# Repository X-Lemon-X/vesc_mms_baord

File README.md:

## Board  addaptr for VESC V6.2 to Modu Card system

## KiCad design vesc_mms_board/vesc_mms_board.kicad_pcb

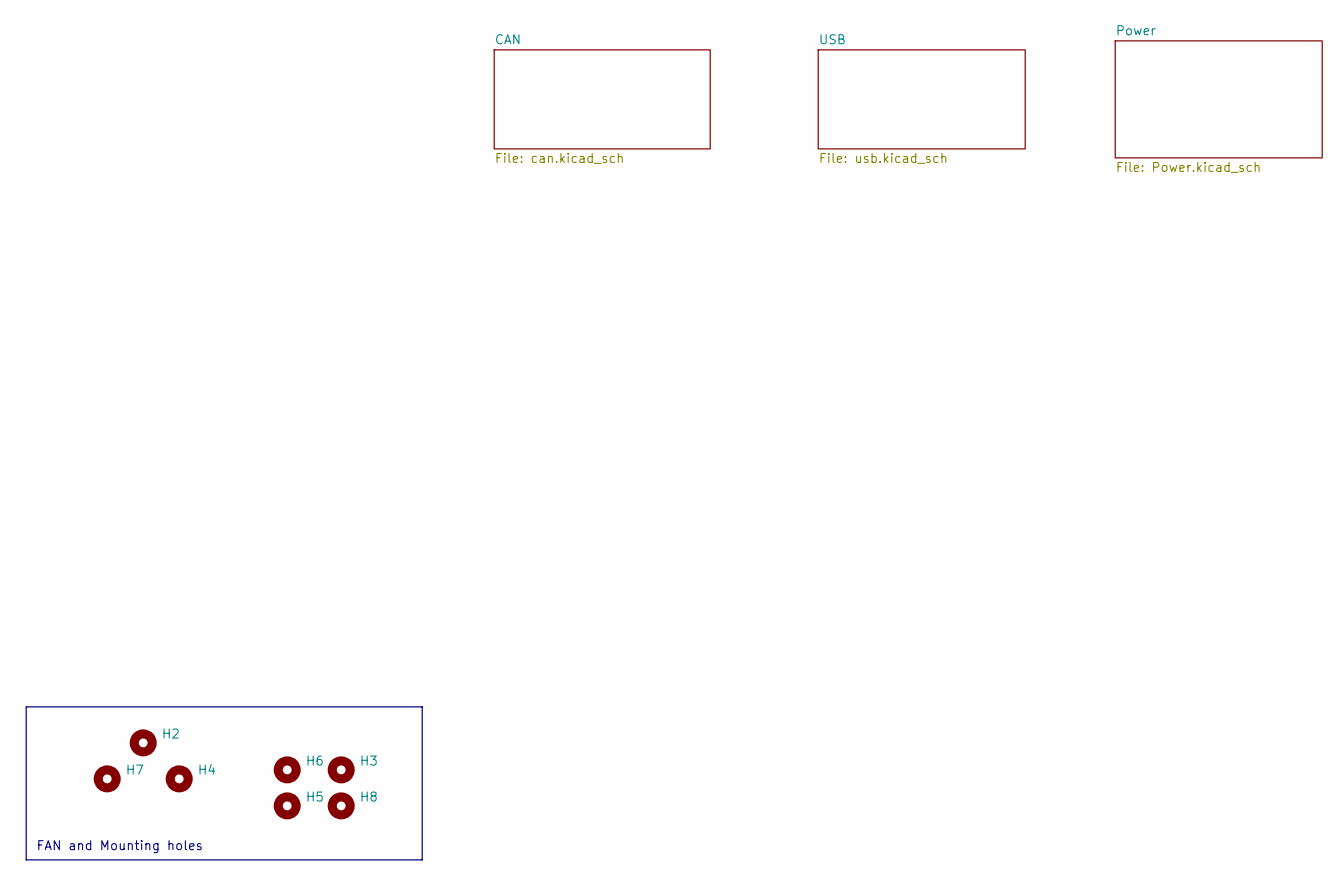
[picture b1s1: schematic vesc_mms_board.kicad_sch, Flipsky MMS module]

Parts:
H2, H4, H7: MountingHole; MountingHole_4.3mm_M4
H3, H5, H6, H8: MountingHole; MountingHole_3.5mm

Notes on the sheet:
FAN and Mounting holes

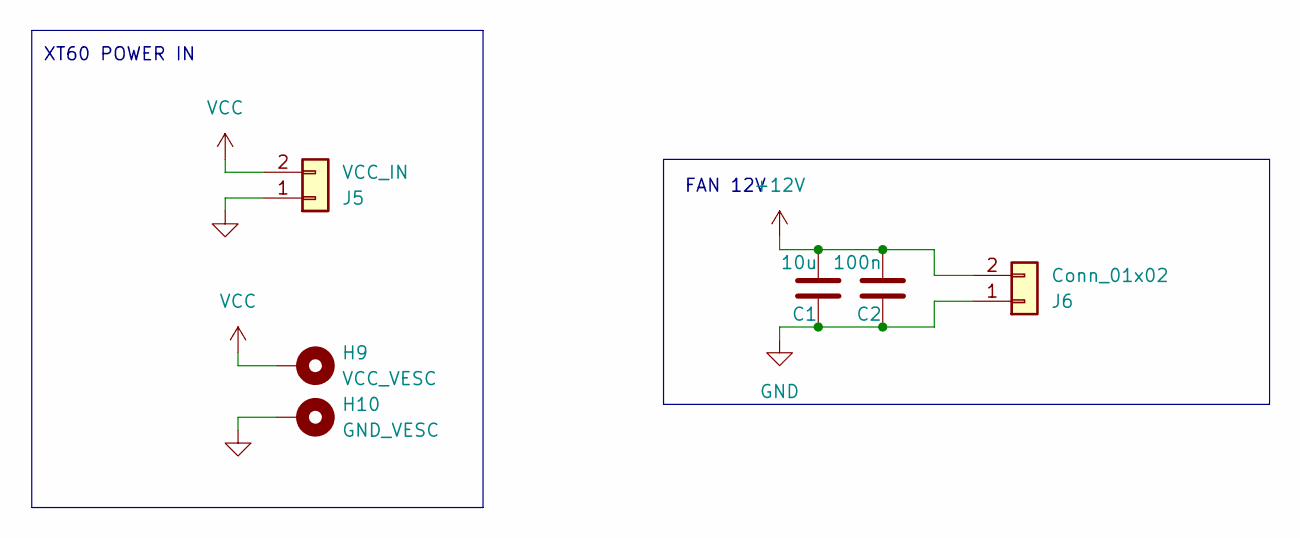
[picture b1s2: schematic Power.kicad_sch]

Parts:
C1: 10u; C_0603_1608Metric
C2: 100n; C_0402_1005Metric
H9: VCC_VESC; MountingHole_4mm_Pad_Via
H10: GND_VESC; MountingHole_4mm_Pad_Via
J5: VCC_IN; AMASS_XT60PW-M_1x02_P7.20mm_Horizontal
J6: Conn_01x02; JST_XH_B2B-XH-A_1x02_P2.50mm_Vertical

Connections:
+12V: C1.2, C2.2, J6.2; also elsewhere on the board
GND: C1.1, C2.1, H10.1, J5.1, J6.1; also elsewhere on the board
VCC: H9.1, J5.2

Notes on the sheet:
FAN 12V
XT60 POWER IN

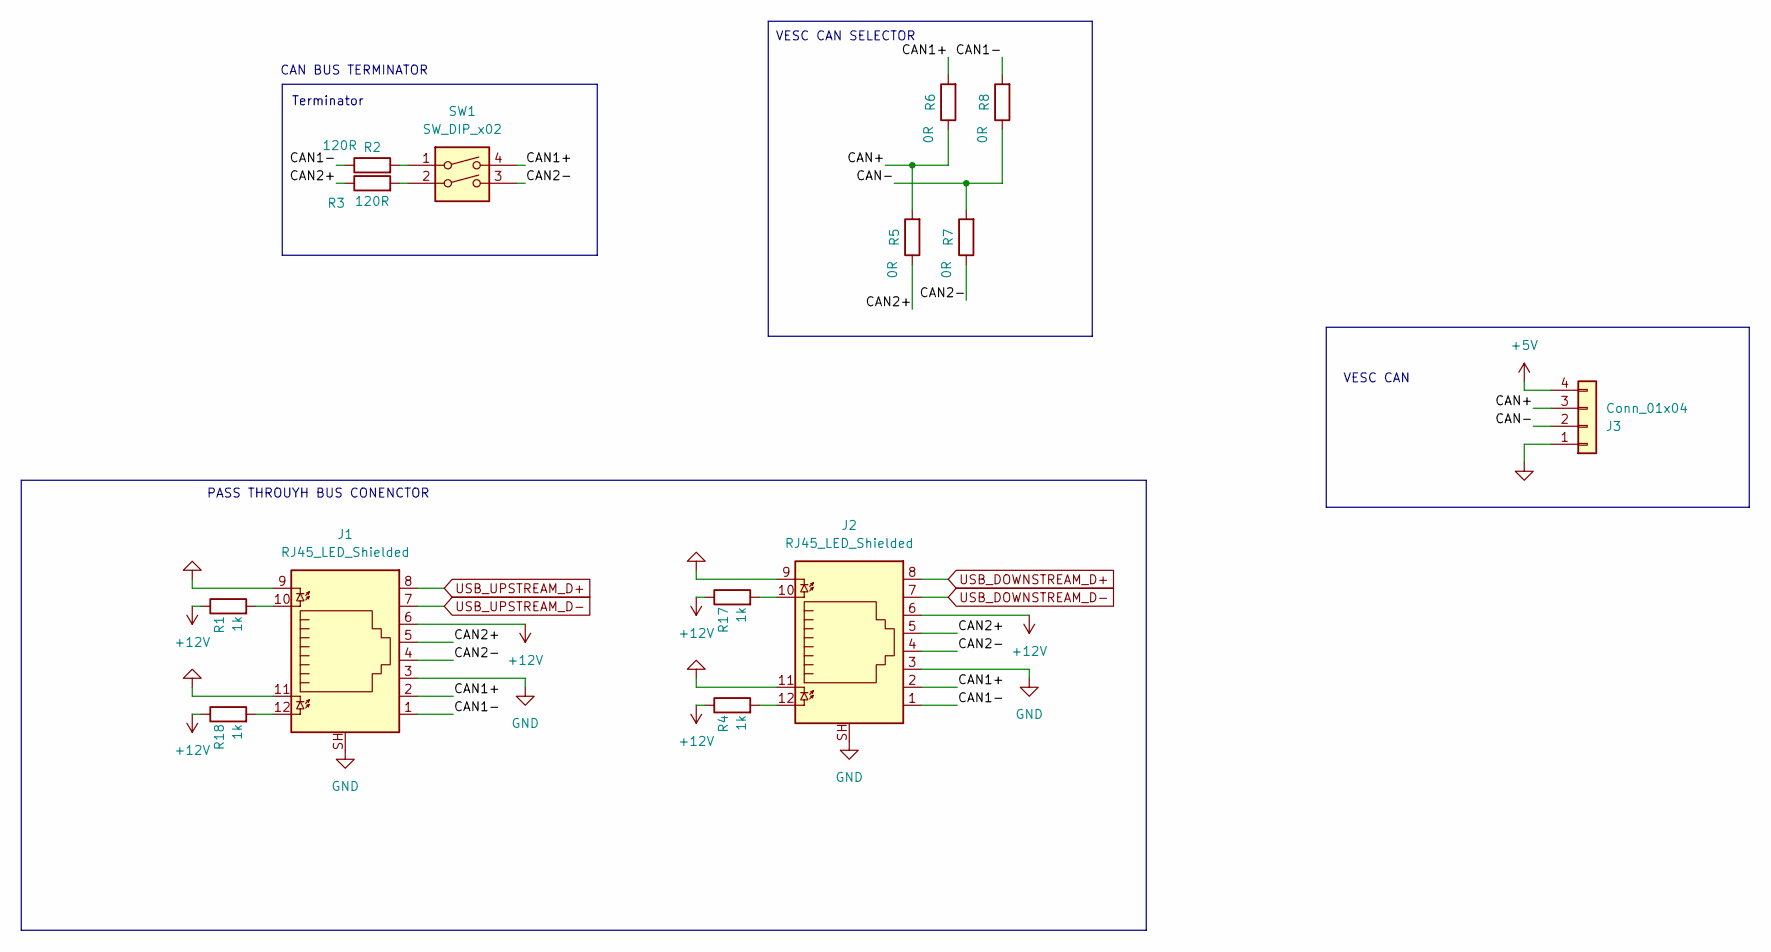
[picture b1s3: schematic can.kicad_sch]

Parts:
J1, J2: RJ45_LED_Shielded; RJ45_Amphenol_RJHSE538X
J3: Conn_01x04; JST_XH_B4B-XH-A_1x04_P2.50mm_Vertical
R1, R4, R17, R18: 1k; R_0402_1005Metric
R2, R3: 120R; R_0603_1608Metric
R5, R6, R7, R8: 0R; R_0603_1608Metric
SW1: SW_DIP_x02; SW_DIP_SPSTx02_Slide_6.7x6.64mm_W7.62mm_P2.54mm_LowProfile

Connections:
+5V: J3.4; also elsewhere on the board
+12V: J1.6, J2.6, R1.1, R4.1, R17.1, R18.1; also elsewhere on the board
/CAN/CAN1+: J1.2, J2.2, R6.2, SW1.4
/CAN/CAN1-: J1.1, J2.1, R2.1, R8.2
/CAN/CAN2+: J1.5, J2.5, R3.1, R5.1
/CAN/CAN2-: J1.4, J2.4, R7.1, SW1.3
/CAN/CAN+: J3.3, R5.2, R6.1
/CAN/CAN-: J3.2, R7.2, R8.1
GND: J1.3, J1.9, J1.11, J1.SH, J2.3, J2.9, J2.11, J2.SH, J3.1; also elsewhere on the board
unnamed: J1.10, R1.2
unnamed: J1.12, R18.2
unnamed: J2.10, R17.2
unnamed: J2.12, R4.2
unnamed: R2.2, SW1.1
unnamed: R3.2, SW1.2
USB_DOWNSTREAM_D+: J2.8; also elsewhere on the board
USB_DOWNSTREAM_D-: J2.7; also elsewhere on the board
USB_UPSTREAM_D+: J1.8; also elsewhere on the board
USB_UPSTREAM_D-: J1.7; also elsewhere on the board

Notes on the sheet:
PASS THROUYH BUS CONENCTOR
CAN BUS TERMINATOR
VESC CAN
Terminator
VESC CAN SELECTOR

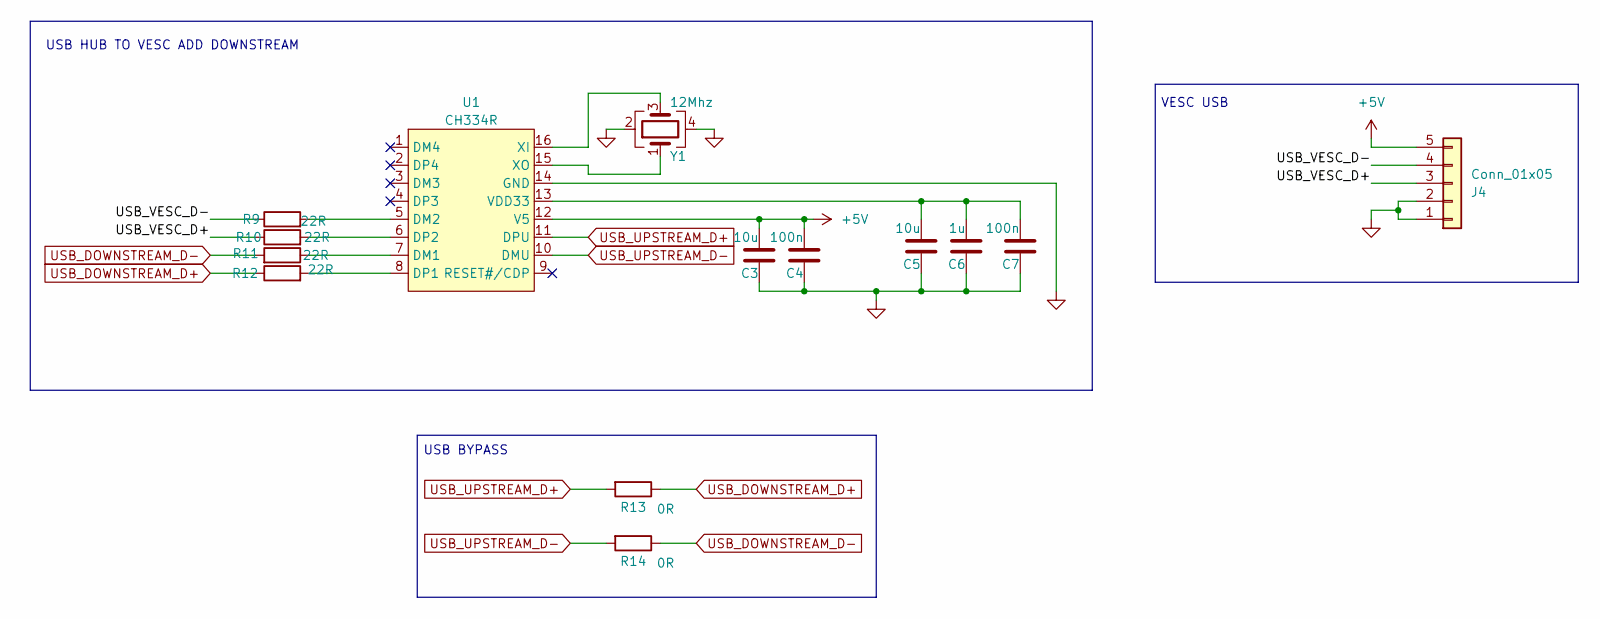
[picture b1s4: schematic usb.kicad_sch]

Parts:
C3, C5: 10u; C_0603_1608Metric
C4, C7: 100n; C_0402_1005Metric
C6: 1u; C_0603_1608Metric
J4: Conn_01x05; JST_XH_B5B-XH-A_1x05_P2.50mm_Vertical
R9, R10, R11, R12: 22R; R_0402_1005Metric
R13, R14: 0R; R_0603_1608Metric
U1: CH334R; QSOP-16_3.9x4.9mm_P0.635mm
Y1: 12Mhz; Crystal_SMD_3225-4Pin_3.2x2.5mm

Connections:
+5V: C3.2, C4.2, J4.5, U1.12 (V5); also elsewhere on the board
/USB/USB_VESC_D+: J4.3, R10.1
/USB/USB_VESC_D-: J4.4, R9.1
GND: C3.1, C4.1, C5.1, C6.1, C7.1, J4.1, J4.2, U1.14 (GND), Y1.2, Y1.4; also elsewhere on the board
unnamed: R11.1, U1.7 (DM1)
unnamed: R9.2, U1.5 (DM2)
unnamed: R12.2, U1.8 (DP1)
unnamed: R10.2, U1.6 (DP2)
unnamed: C5.2, C6.2, C7.2, U1.13 (VDD33)
unnamed: U1.16 (XI), Y1.3
unnamed: U1.15 (XO), Y1.1
USB_DOWNSTREAM_D+: R12.1, R13.1; also elsewhere on the board
USB_DOWNSTREAM_D-: R11.2, R14.1; also elsewhere on the board
USB_UPSTREAM_D+: R13.2, U1.11 (DPU); also elsewhere on the board
USB_UPSTREAM_D-: R14.2, U1.10 (DMU); also elsewhere on the board

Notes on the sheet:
USB BYPASS
USB HUB TO VESC ADD DOWNSTREAM
VESC USB

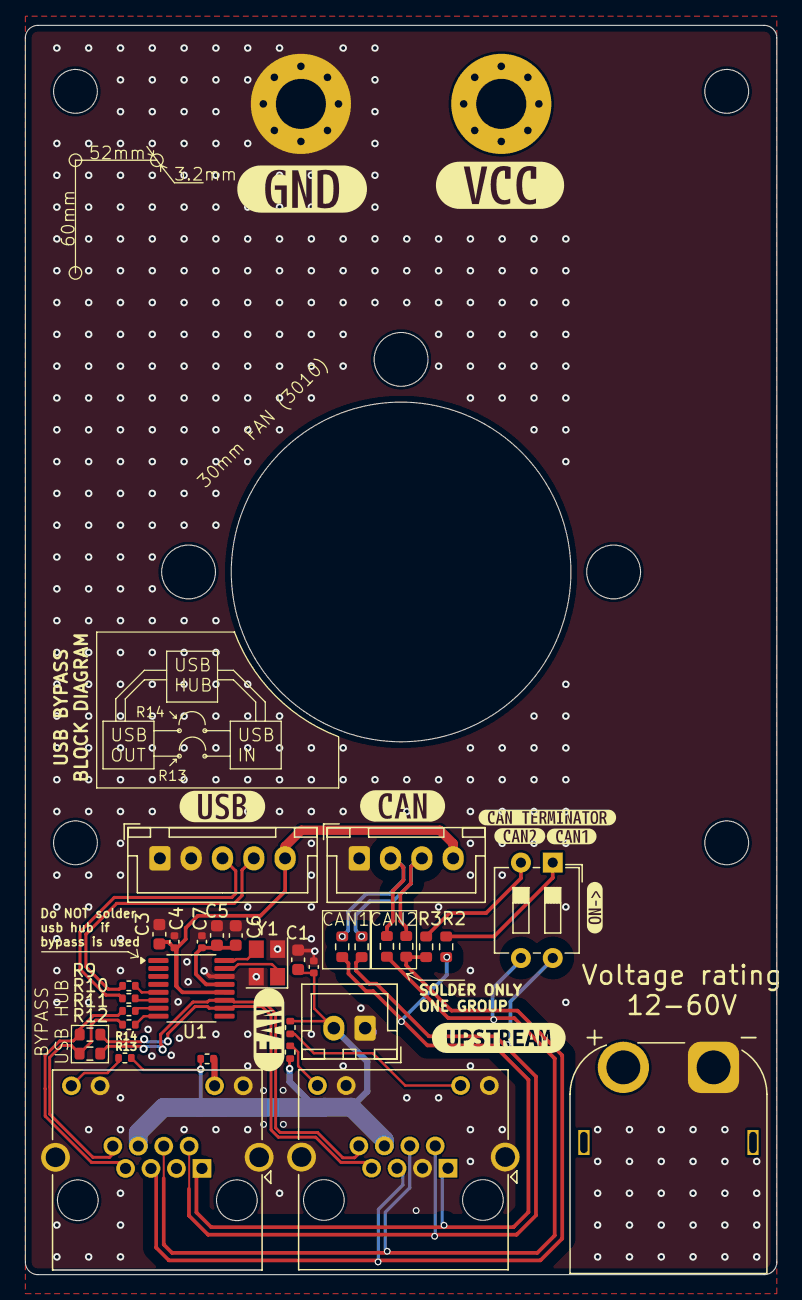
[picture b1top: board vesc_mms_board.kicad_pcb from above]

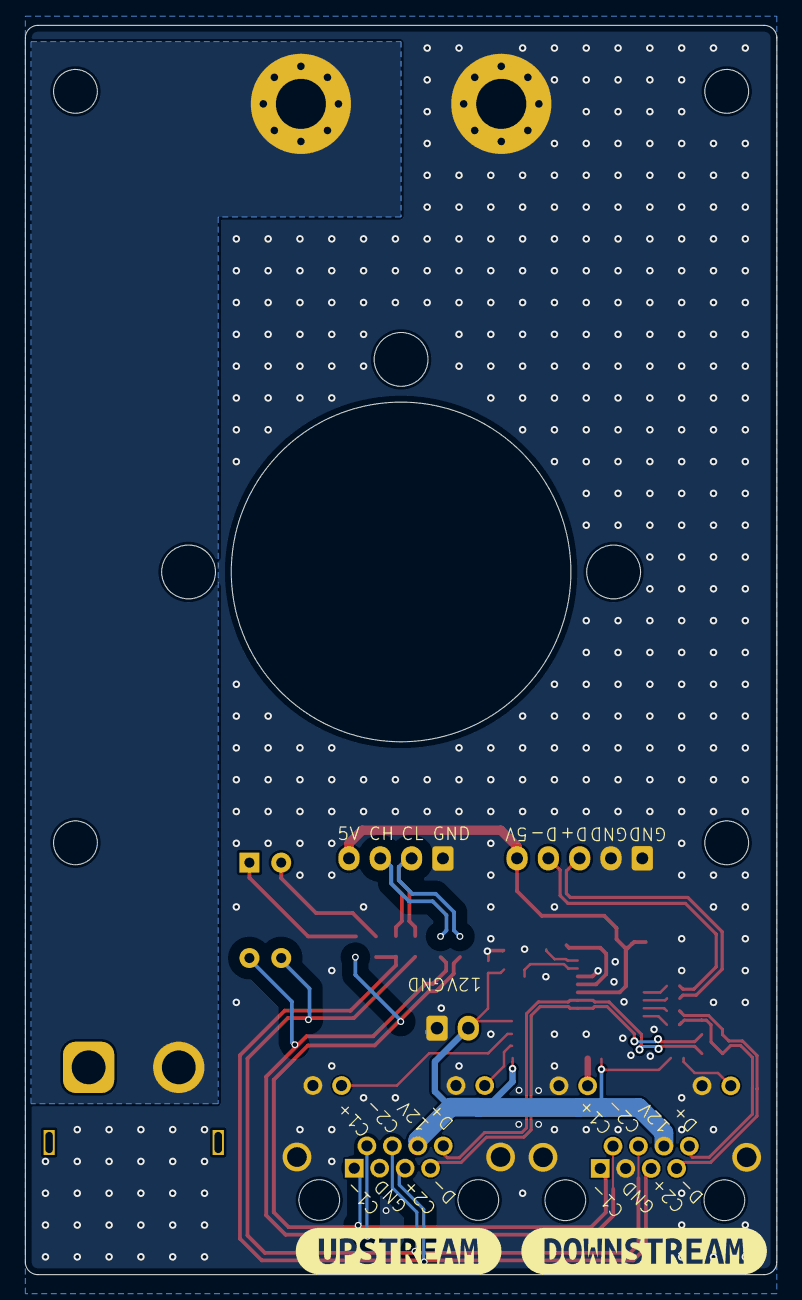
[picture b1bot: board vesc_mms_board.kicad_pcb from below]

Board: 2 copper layers, 60.0 x 99.7 mm, 53 parts (2 on the bottom side), 29 nets.

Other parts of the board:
kibuzzard-674E452F: G***; kibuzzard-674E452F
kibuzzard-674E462A: G***; kibuzzard-674E462A
kibuzzard-674E4526: G***; kibuzzard-674E4526
kibuzzard-674E4620: G***; kibuzzard-674E4620
kibuzzard-674E4631: G***; kibuzzard-674E4631
kibuzzard-675D9C7D: G***; kibuzzard-675D9C7D
kibuzzard-675D9C67: G***; kibuzzard-675D9C67
kibuzzard-675D9C73: G***; kibuzzard-675D9C73
kibuzzard-675D9CCD: G***; kibuzzard-675D9CCD
kibuzzard-673147F0: G***; kibuzzard-673147F0
kibuzzard-6754762D: G***; kibuzzard-6754762D
kibuzzard-67314807: G***; kibuzzard-67314807

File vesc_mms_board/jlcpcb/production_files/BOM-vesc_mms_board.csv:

Comment,Designator,Footprint,LCSC,Quantity
CH334R,U1,QSOP-16_3.9x4.9mm_P0.635mm,,1
100n,C2,C_0402_1005Metric,,1
10u,C5,C_0603_1608Metric,,1
SW_DIP_x02,SW1,SW_DIP_SPSTx02_Slide_6.7x6.64mm_W7.62mm_P2.54mm_LowProfile,,1
22R,R11,R_0402_1005Metric,,1
0R,R8,R_0603_1608Metric,,1
120R,R2,R_0603_1608Metric,,1
22R,R12,R_0402_1005Metric,,1
120R,R3,R_0603_1608Metric,,1
Conn_01x05,J4,JST_XH_B5B-XH-A_1x05_P2.50mm_Vertical,,1
VCC_IN,J5,AMASS_XT60PW-M_1x02_P7.20mm_Horizontal,,1
10u,C1,C_0603_1608Metric,,1
12Mhz,Y1,Crystal_SMD_3225-4Pin_3.2x2.5mm,,1
22R,R9,R_0402_1005Metric,,1
0R,R6,R_0603_1608Metric,,1
1u,C6,C_0603_1608Metric,,1
10u,C3,C_0603_1608Metric,,1
100n,C4,C_0402_1005Metric,,1
Conn_01x02,J6,JST_XH_B2B-XH-A_1x02_P2.50mm_Vertical,,1
100n,C7,C_0402_1005Metric,,1
0R,R7,R_0603_1608Metric,,1
0R,R5,R_0603_1608Metric,,1
22R,R10,R_0402_1005Metric,,1
0R,R13,R_0603_1608Metric,,1
RJ45_LED_Shielded,J1,RJ45_Amphenol_RJHSE538X,,1
RJ45_LED_Shielded,J2,RJ45_Amphenol_RJHSE538X,,1
0R,R14,R_0603_1608Metric,,1
1k,R17,R_0402_1005Metric,,1
1k,R18,R_0402_1005Metric,,1
Conn_01x04,J3,JST_XH_B4B-XH-A_1x04_P2.50mm_Vertical,,1
1k,R1,R_0402_1005Metric,,1
1k,R4,R_0402_1005Metric,,1

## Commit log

2024-12-02 init
2024-12-03 pcb created
2024-12-08 fianl
2024-12-14 cehnaged leyour added vias
2024-12-14 update tetx
2024-12-14 updaet text
2024-12-16 updarte readme final desing rev a
2025-02-14 Update rev 2.0, added step files
2025-02-15 fixed problem with xt60
2025-09-09 fixed xt60 connvetor
2025-09-09 added gerber files
2025-09-26 update step
